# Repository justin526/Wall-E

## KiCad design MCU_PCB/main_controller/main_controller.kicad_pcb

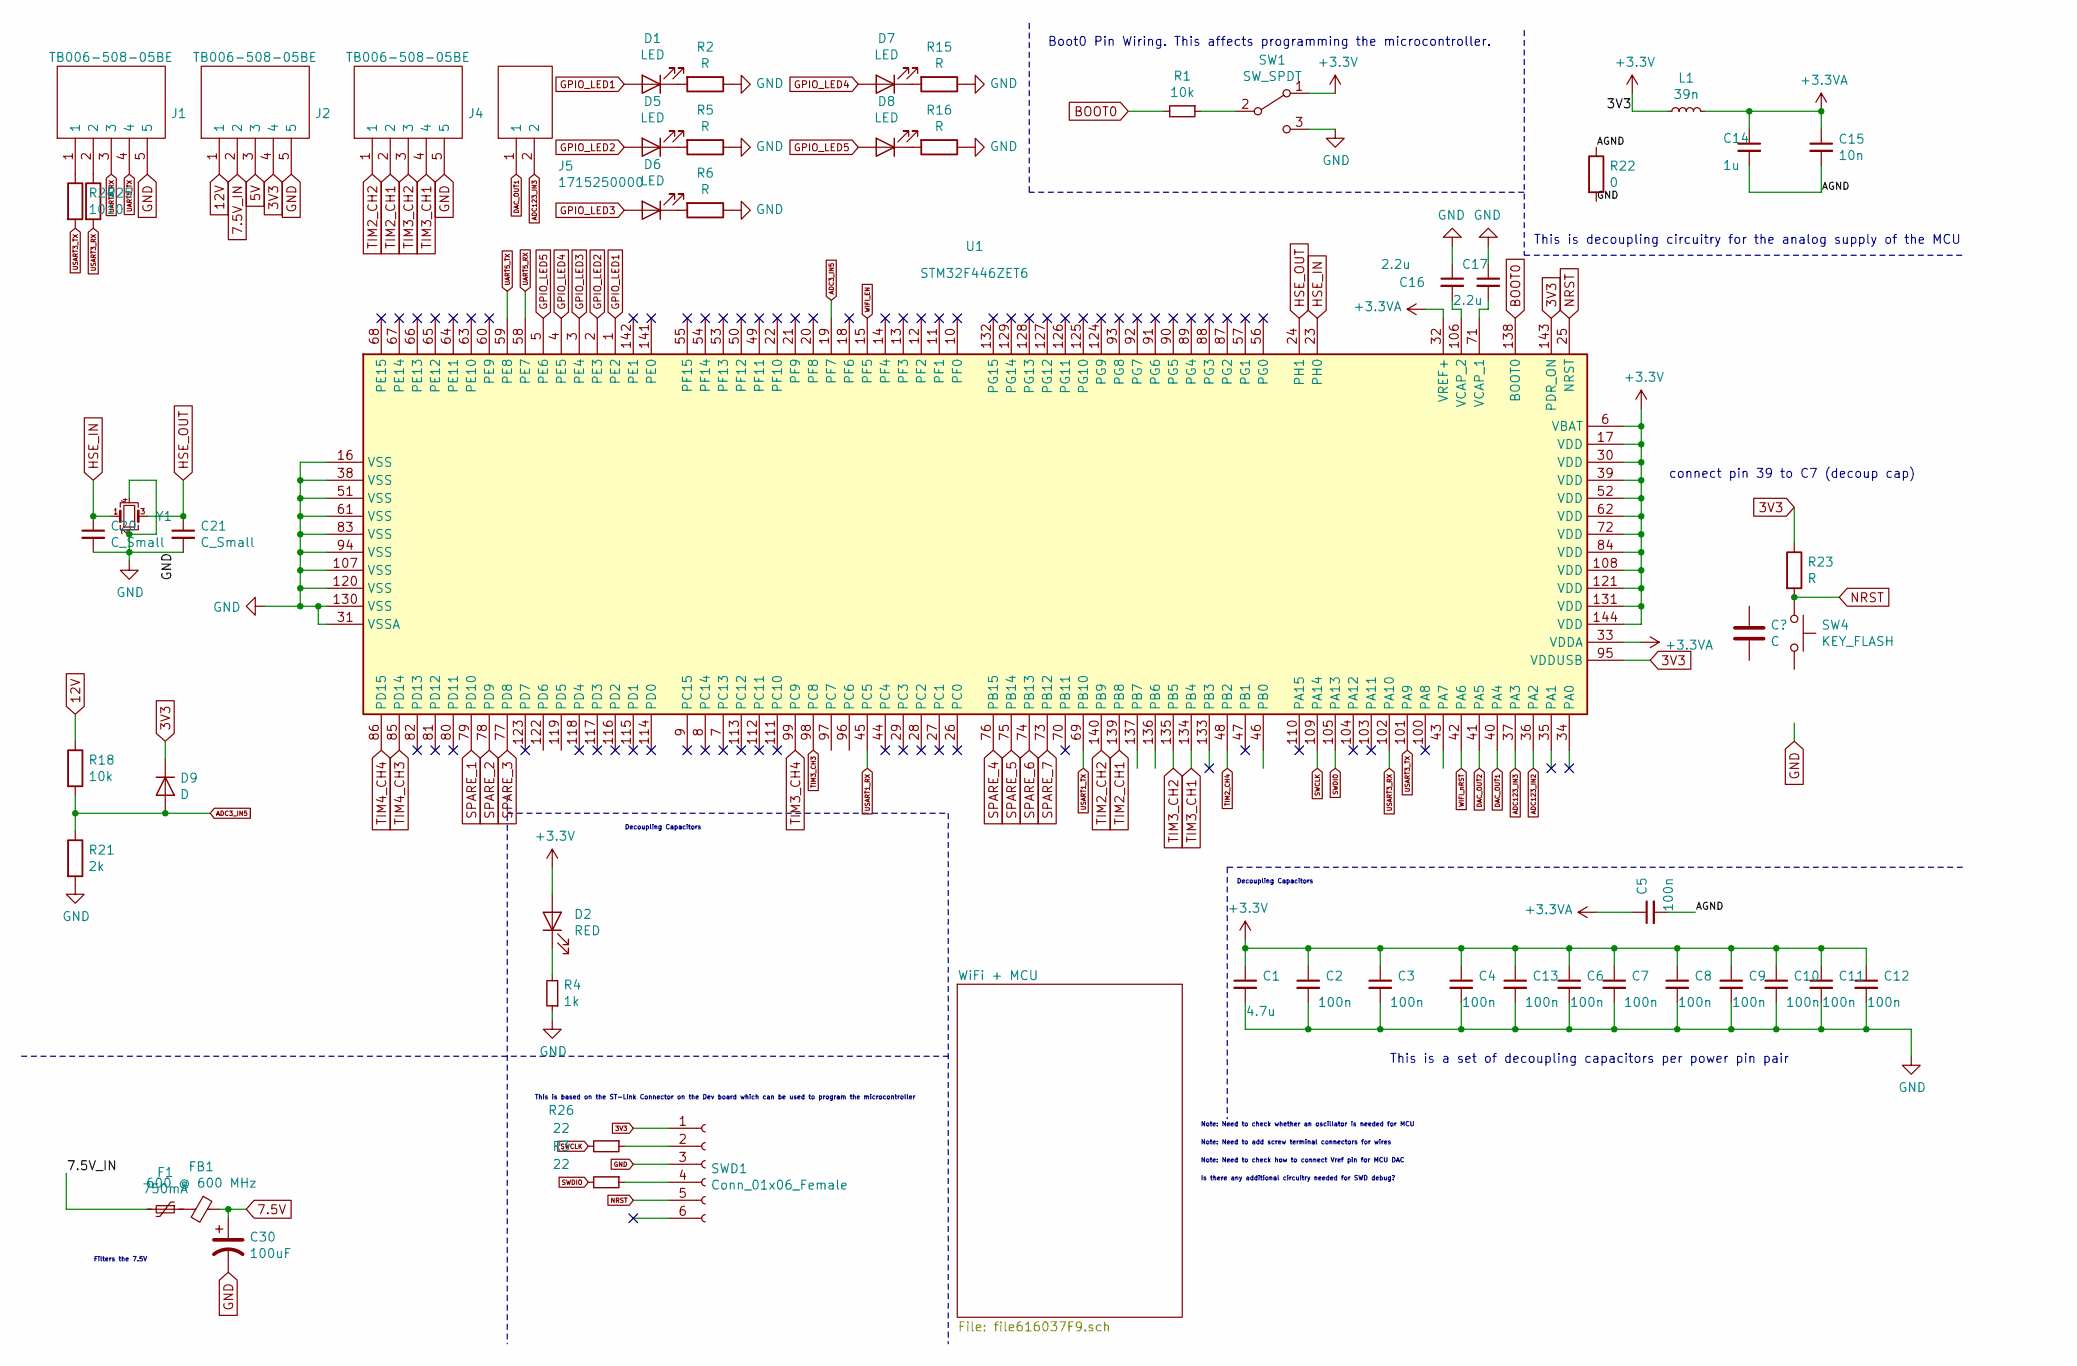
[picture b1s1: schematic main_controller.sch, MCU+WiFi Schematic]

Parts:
C1: 4.7u; C_0805_2012Metric
C2, C3, C4, C5, C6, C7, C8, C9, C10, C11, C12, C13: 100n; C_0805_2012Metric
C14: 1u; C_0805_2012Metric
C15: 10n; C_0805_2012Metric
C16, C17: 2.2u; C_0805_2012Metric
C20, C21: C_Small; C_0805_2012Metric
C30: 100uF; CAP_EEEHA0J101WR
D1, D5, D6, D7, D8: LED; LED_0805_2012Metric
D2: RED; LED_0805_2012Metric
D9: D; D_0805_2012Metric
F1: 750mA; R_1210_3225Metric
FB1: 600 @ 600 MHz; R_0603_1608Metric
J1, J2, J4: TB006-508-05BE; SHDR5W100P0X508_1X5_2540X820X1000P; Mouser Part Number 490-TB006-508-05BE
J5: 1715250000; Mouser Part Number 470-1715250000
L1: 39n; L_0402_1005Metric
R1, R18: 10k; R_0805_2012Metric
R2, R5, R6, R15, R16, R23: R; R_0805_2012Metric
R3, R26: 22; R_0805_2012Metric
R4: 1k; R_0805_2012Metric
R21: 2k; R_0805_2012Metric
R22: 0; R_0805_2012Metric
R24, R25: 10; R_0805_2012Metric
SW1: SW_SPDT; 118251376
SW4: KEY_FLASH; SW_147873-2
SWD1: Conn_01x06_Female; PinHeader_1x06_P2.54mm_Vertical
U1: STM32F446ZET6; LQFP-144_20x20mm_P0.5mm
Y1: Crystal_GND24_Small; EA1620LA1216000MTR

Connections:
3V3: C1.1, C2.1, C3.1, C4.1, C6.1, C7.1, C8.1, C9.1, C10.1, C11.1, C12.1, C13.1, D2.2 (A), D9.1 (K), J2.4, L1.1, R23.1, SW1.1 (A), SWD1.1, U1.6 (VBAT), U1.17 (VDD), U1.30 (VDD), U1.39 (VDD), U1.42 (PA6), U1.52 (VDD), U1.62 (VDD), U1.72 (VDD), U1.84 (VDD), U1.95 (VDDUSB), U1.108 (VDD), U1.121 (VDD), U1.131 (VDD), U1.143 (PDR_ON), U1.144 (VDD); also elsewhere on the board
5V: J2.3; also elsewhere on the board
7.5V: C30.1, FB1.1; also elsewhere on the board
7.5V_IN: F1.2, J2.2
12V: J2.1, R18.1
+3.3VA: C5.1, C14.1, C15.1, L1.2, U1.32 (VREF+), U1.33 (VDDA)
/AGND: C5.2, C14.2, C15.2, R22.1
ADC3_IN5: D9.2 (A), R18.2, R21.1, U1.19 (PF7)
ADC123_IN2: U1.36 (PA2)
ADC123_IN3: J5.2, U1.37 (PA3)
BOOT0: R1.2, U1.138 (BOOT0)
DAC_OUT1: J5.1, U1.40 (PA4)
DAC_OUT2: U1.41 (PA5)
GND: C1.2, C2.2, C3.2, C4.2, C6.2, C7.2, C8.2, C9.2, C10.2, C11.2, C12.2, C13.2, C16.1, C17.1, C20.2, C21.2, C30.2, J1.5, J2.5, J4.5, R2.1, R4.1, R5.1, R6.1, R15.1, R16.1, R21.2, R22.2, SW1.3 (C), SW4.2, SWD1.3, U1.16 (VSS), U1.31 (VSSA), U1.38 (VSS), U1.51 (VSS), U1.61 (VSS), U1.83 (VSS), U1.94 (VSS), U1.107 (VSS), U1.120 (VSS), U1.130 (VSS), Y1.2, Y1.4; also elsewhere on the board
GPIO_LED1: D1.2 (A), U1.1 (PE2)
GPIO_LED2: D5.2 (A), U1.2 (PE3)
GPIO_LED3: D6.2 (A), U1.3 (PE4)
GPIO_LED4: D7.2 (A), U1.4 (PE5)
GPIO_LED5: D8.2 (A), U1.5 (PE6)
HSE_IN: C20.1, U1.23 (PH0), Y1.1
HSE_OUT: C21.1, U1.24 (PH1), Y1.3
NRST: R23.2, SW4.1, SWD1.5, U1.25 (NRST)
unnamed: C16.2, U1.106 (VCAP_2)
unnamed: C17.2, U1.71 (VCAP_1)
unnamed: D1.1 (K), R2.2
unnamed: D2.1 (K), R4.2
unnamed: D5.1 (K), R5.2
unnamed: D6.1 (K), R6.2
unnamed: D7.1 (K), R15.2
unnamed: D8.1 (K), R16.2
unnamed: F1.1, FB1.2
unnamed: J1.1, R24.1
unnamed: J1.2, R25.1
unnamed: R1.1, SW1.2 (B)
unnamed: R3.1, SWD1.4
unnamed: R26.1, SWD1.2
SPARE_1: U1.79 (PD10)
SPARE_2: U1.78 (PD9)
SPARE_3: U1.77 (PD8)
SPARE_4: U1.76 (PB15)
SPARE_5: U1.75 (PB14)
SPARE_6: U1.74 (PB13)
SPARE_7: U1.73 (PB12)
SWCLK: R26.2, U1.109 (PA14)
SWDIO: R3.2, U1.105 (PA13)
TIM2_CH1: J4.2, U1.139 (PB8)
TIM2_CH2: J4.1, U1.140 (PB9)
TIM2_CH4: U1.48 (PB2)
TIM3_CH1: J4.4, U1.134 (PB4)
TIM3_CH2: J4.3, U1.135 (PB5)
TIM3_CH3: U1.98 (PC8)
TIM3_CH4: U1.99 (PC9)
TIM4_CH3: U1.85 (PD14)
TIM4_CH4: U1.86 (PD15)
UART5_RX: J1.3, U1.58 (PE7)
UART5_TX: J1.4, U1.59 (PE8)
USART1_RX: U1.45 (PC5); also elsewhere on the board
USART1_TX: U1.69 (PB10); also elsewhere on the board
USART3_RX: R25.2, U1.102 (PA10)
USART3_TX: R24.2, U1.101 (PA9)
WIFI_EN: U1.15 (PF5); also elsewhere on the board

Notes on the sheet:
Boot0 Pin Wiring. This affects programming the microcontroller.
This is a set of decoupling capacitors per power pin pair
This is decoupling circuitry for the analog supply of the MCU
Note: Need to check whether an oscillator is needed for MCU
Filters the 7.5V
This is based on the ST-Link Connector on the Dev board which can be used to program the microcontroller
Note: Need to add screw terminal connectors for wires
Note: Need to check how to connect Vref pin for MCU DAC
Is there any additional circuitry needed for SWD debug?
Decoupling Capacitors
connect pin 39 to C7 (decoup cap)

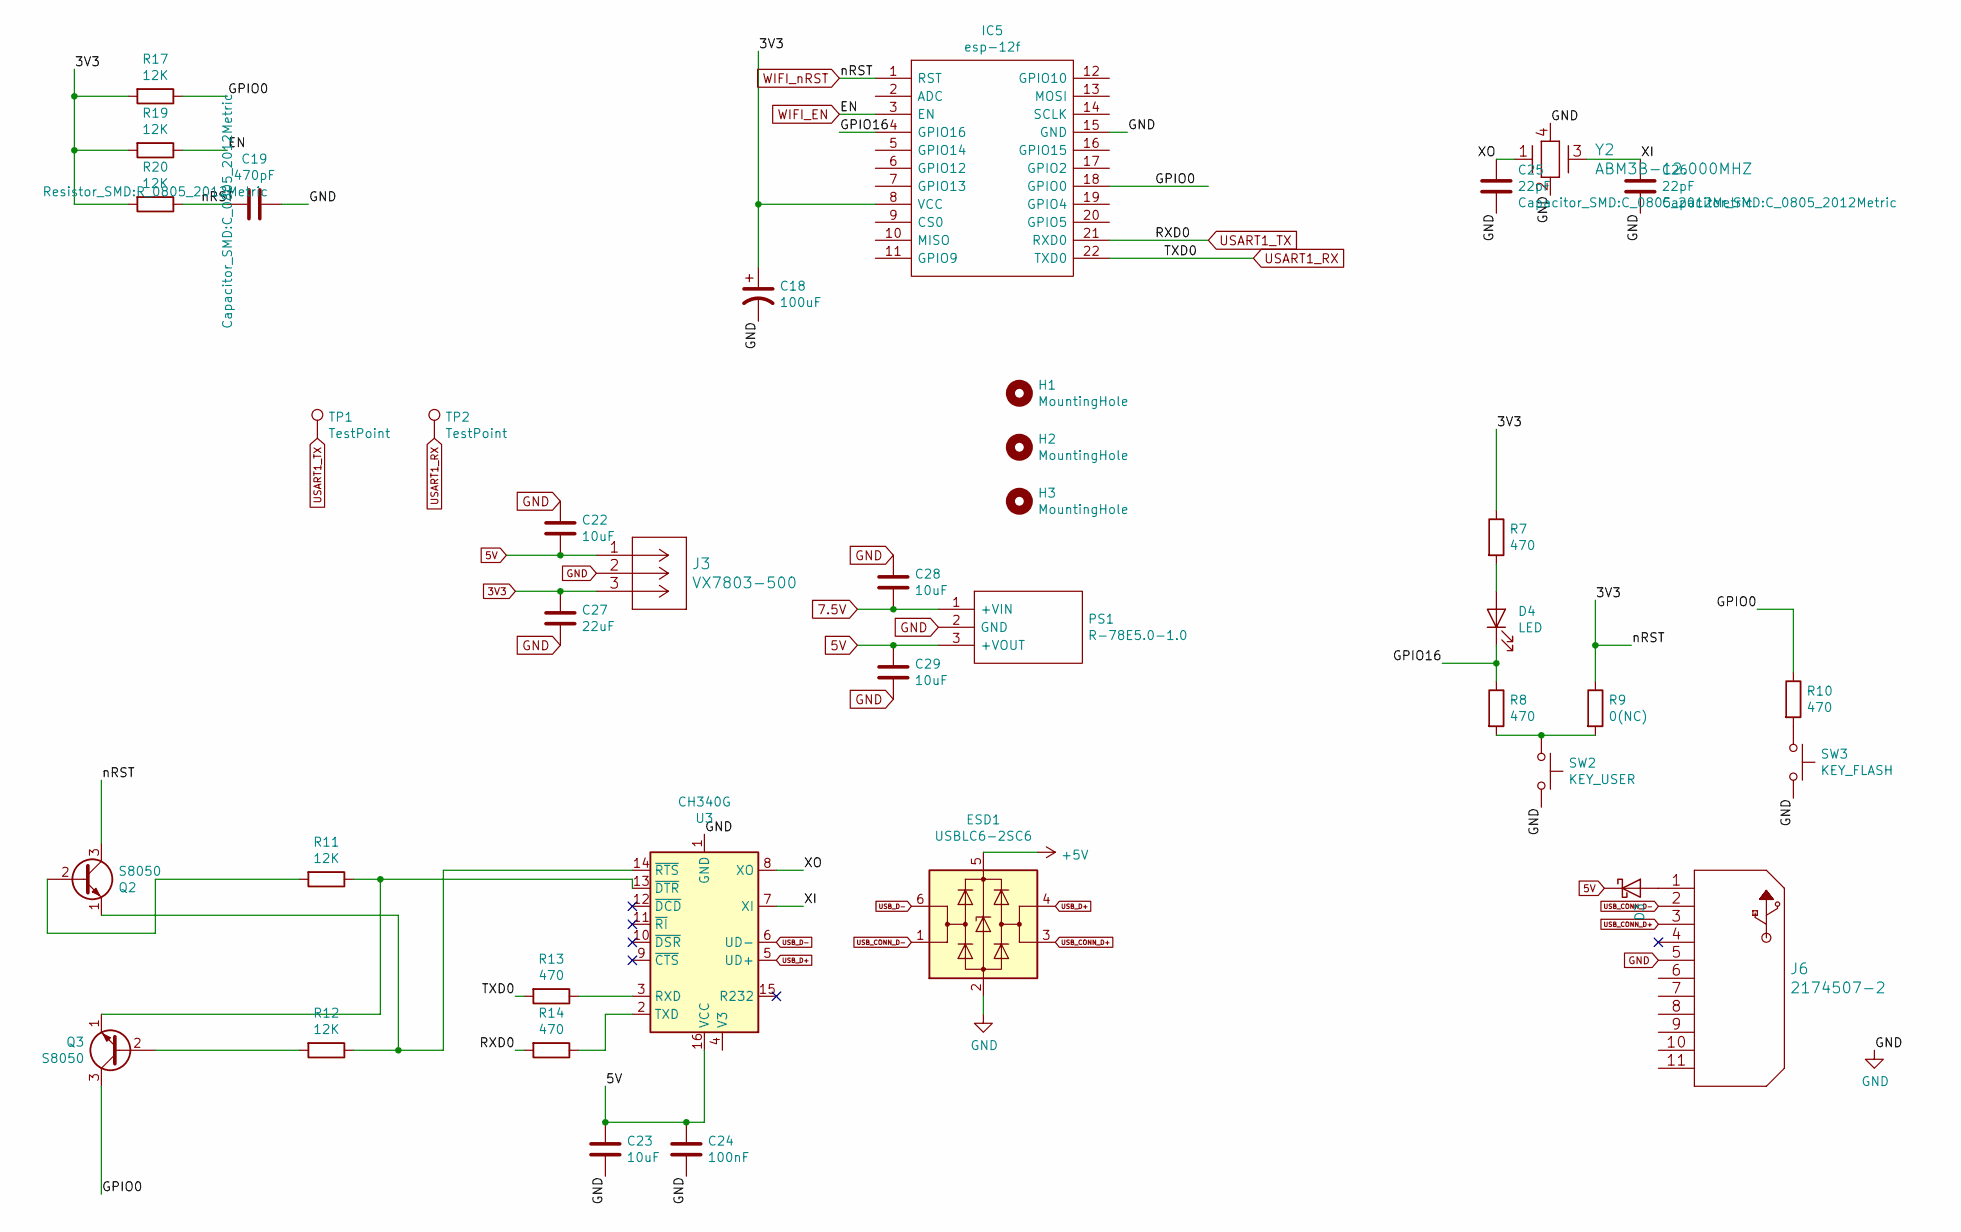
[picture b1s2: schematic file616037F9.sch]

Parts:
C18: 100uF; CAP_EEEHA0J101WR
C19: 470pF; C_0805_2012Metric
C22, C28, C29: 10uF; C_1210_3225Metric
C23: 10uF; C_0805_2012Metric
C24: 100nF; C_0805_2012Metric
C25, C26: 22pF; C_0805_2012Metric
C27: 22uF; C_1210_3225Metric
D3: D_Schottky; 1N4007G-T
D4: LED; LED_0805_2012Metric
ESD1: USBLC6-2SC6; SOT-23-6
H1, H2, H3: MountingHole; MountingHole_2.2mm_M2
IC5: esp-12f; esp12f; Manufacturer_Part_Number esp-12f
J3: VX7803-500
J6: 2174507-2
PS1: R-78E5.0-1.0; R78E5010; Mouser Part Number 919-R-78E5.0-1.0
Q2, Q3: S8050; TO-92_Inline
R7, R8, R10, R13, R14: 470; R_0805_2012Metric
R9: 0(NC); R_0805_2012Metric
R11, R12, R17, R19, R20: 12K; R_0805_2012Metric
SW2: KEY_USER; SW_147873-2
SW3: KEY_FLASH; SW_147873-2
TP1, TP2: TestPoint; KEYSTONE_5000
U3: CH340G; SOIC-16_3.9x9.9mm_P1.27mm
Y2: ABM3B-12.000MHZ

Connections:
3V3: C18.1, C19.2, C27.1, IC5.1 (RST), IC5.8 (VCC), J3.3, Q2.3 (C), R7.1, R9.1, R17.2, R19.2, R20.1, R20.2; also elsewhere on the board
5V: C22.2, C23.1, C24.1, C29.1, D3.1 (K), J3.1, PS1.3 (+VOUT), U3.16 (VCC); also elsewhere on the board
7.5V: C28.2, PS1.1 (+VIN); also elsewhere on the board
+5V: ESD1.5 (VBUS)
/WiFi + MCU/GPIO0: IC5.18 (GPIO0), Q3.3 (C), R10.1, R17.1
/WiFi + MCU/GPIO16: D4.1 (K), IC5.4 (GPIO16), R8.1
/WiFi + MCU/XI: C26.1, U3.7 (XI), Y2.3 (2)
/WiFi + MCU/XO: C25.1, U3.8 (XO), Y2.1
GND: C18.2, C19.1, C22.1, C23.2, C24.2, C25.2, C26.2, C27.2, C28.1, C29.2, ESD1.2 (GND), IC5.15 (GND), J3.2, J6.5, PS1.2 (GND), SW2.2, SW3.2, U3.1 (GND), Y2.2 (GND), Y2.4 (GND); also elsewhere on the board
unnamed: D3.2 (A), J6.1
unnamed: D4.2 (A), R7.2
unnamed: Q2.1 (E), R12.1, U3.14 (~RTS)
unnamed: Q2.2 (B), R11.2
unnamed: Q3.1 (E), R11.1, U3.13 (~DTR)
unnamed: Q3.2 (B), R12.2
unnamed: R8.2, R9.2, SW2.1
unnamed: R10.2, SW3.1
unnamed: R13.1, U3.3 (RXD)
unnamed: R14.1, U3.2 (TXD)
USART1_RX: IC5.22 (TXD0), R13.2, TP2.1; also elsewhere on the board
USART1_TX: IC5.21 (RXD0), R14.2, TP1.1; also elsewhere on the board
USB_CONN_D+: ESD1.3 (I/O2), J6.3
USB_CONN_D-: ESD1.1 (I/O1), J6.2
USB_D+: ESD1.4 (I/O2), U3.5 (UD+)
USB_D-: ESD1.6 (I/O1), U3.6 (UD-)
WIFI_EN: IC5.3 (EN), R19.1; also elsewhere on the board

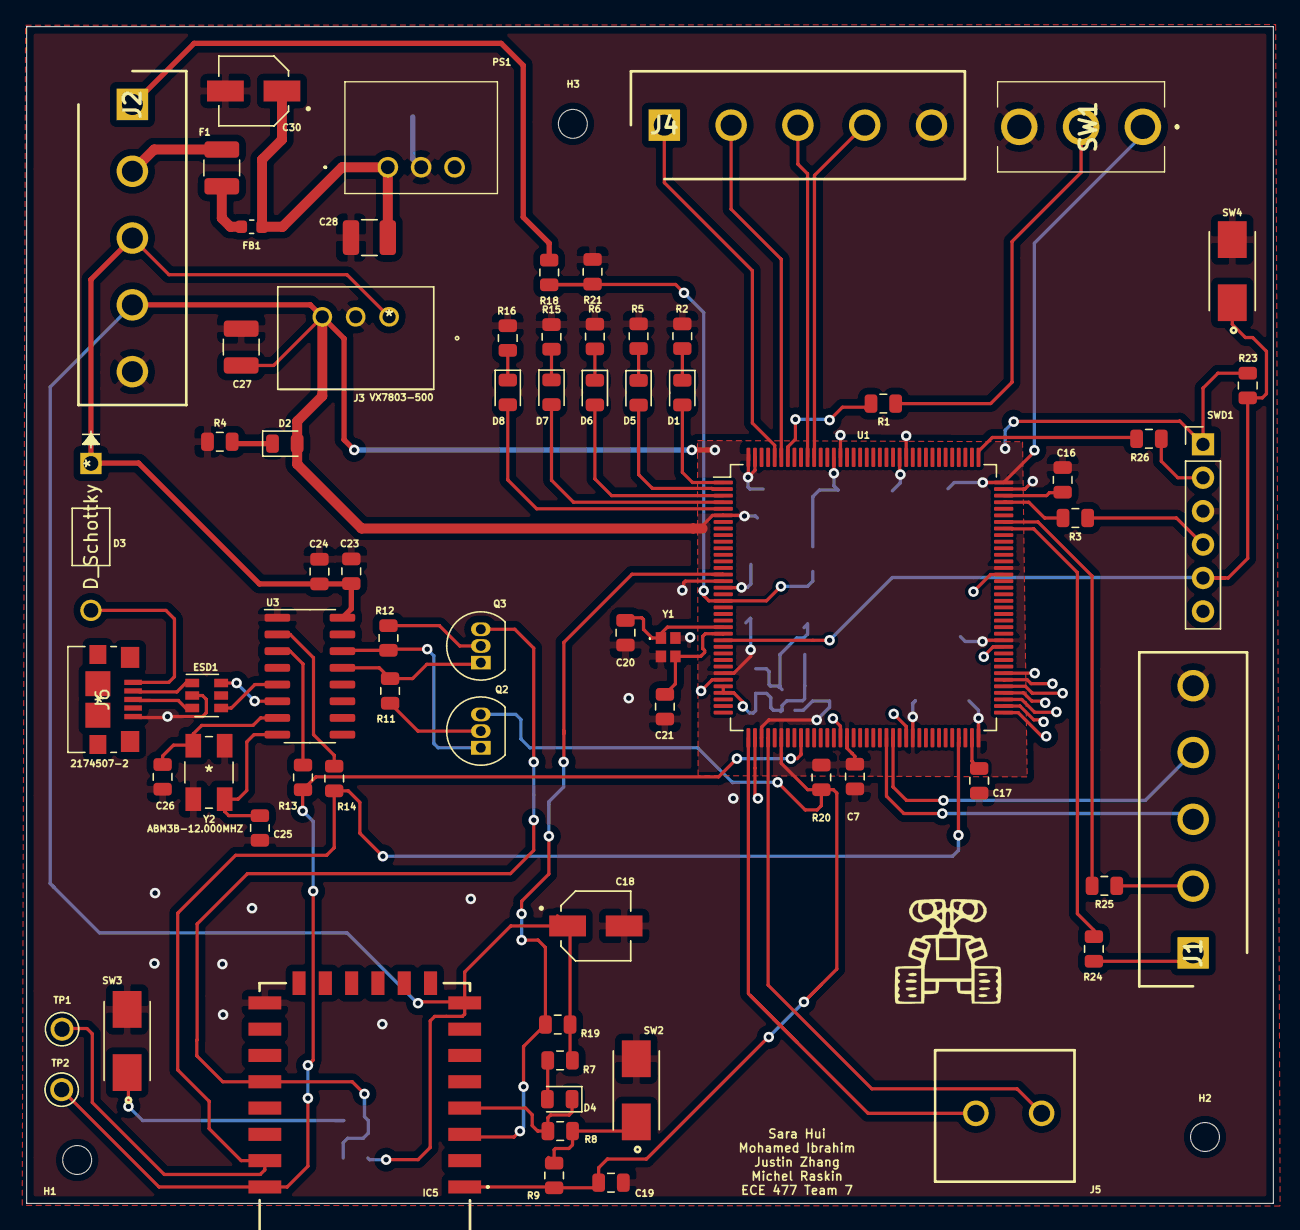
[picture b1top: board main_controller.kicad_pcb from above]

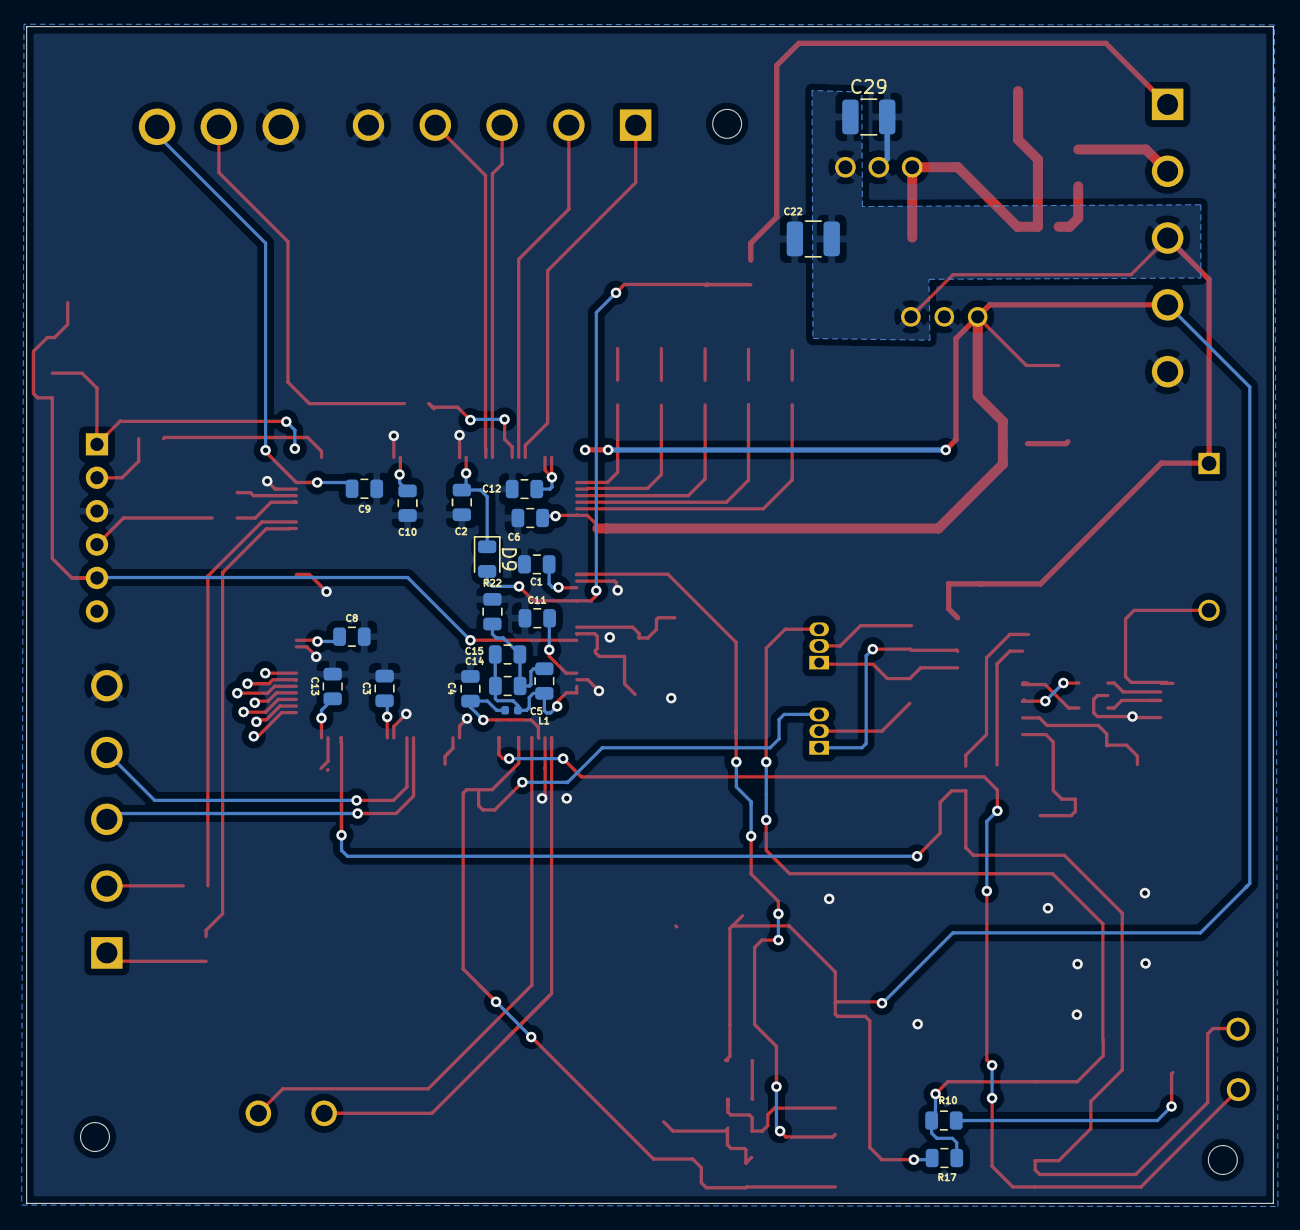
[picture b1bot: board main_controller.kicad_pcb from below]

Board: 2 copper layers, 94.8 x 89.5 mm, 93 parts (21 on the bottom side), 65 nets.

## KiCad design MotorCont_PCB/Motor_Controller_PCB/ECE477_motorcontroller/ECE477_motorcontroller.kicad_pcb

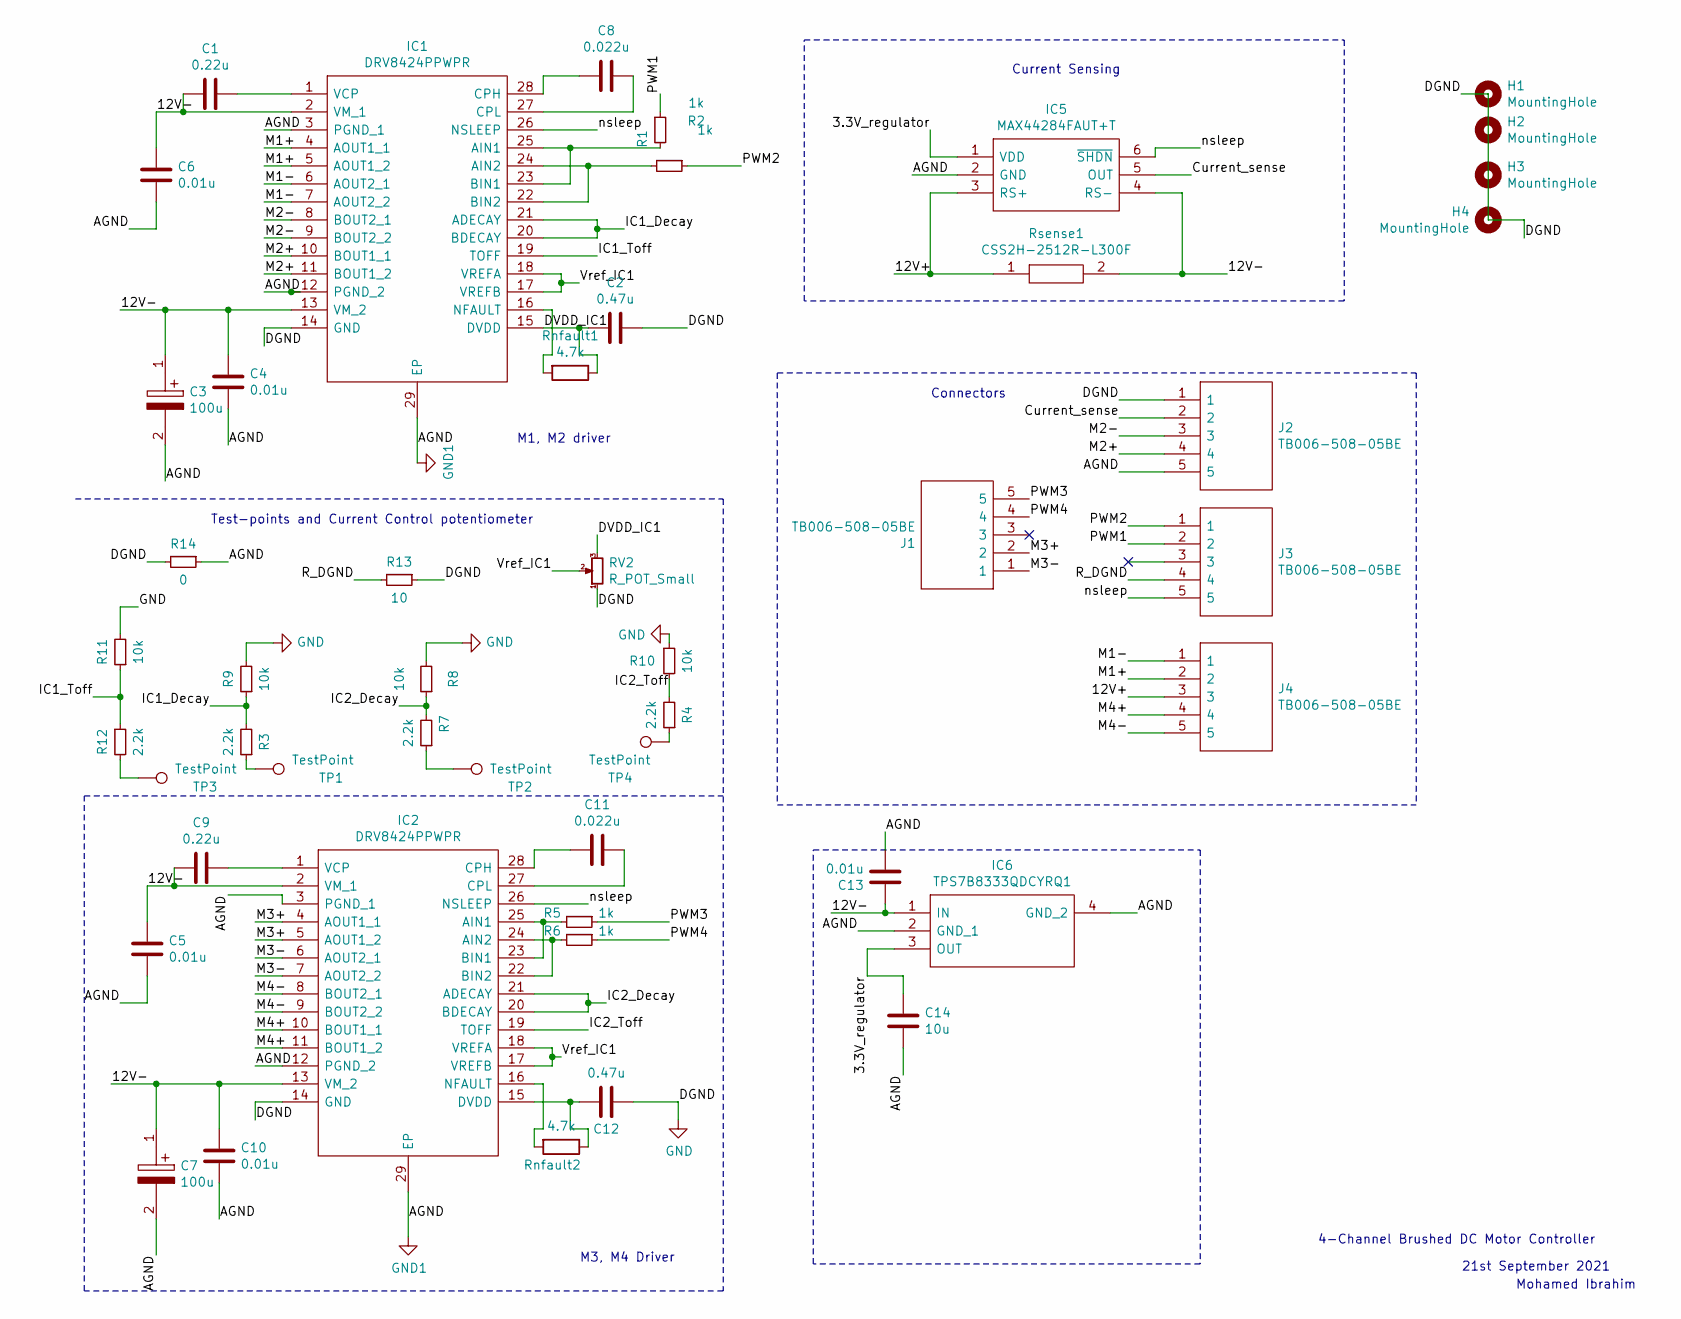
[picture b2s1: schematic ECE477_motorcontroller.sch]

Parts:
C1, C9: 0.22u; CAPC1005X55N
C2, C12: 0.47u; CAPC1005X55N
C3, C7: 100u; CAPPRD350W60D840H1350; Mouser Part Number 647-UBT1C101MPD8TD
C4, C5, C6, C10, C13: 0.01u; CAPC1005X55N
C8, C11: 0.022u; CAPC3216X88N
C14: 10u; C_1210_3225Metric
H1, H2, H3, H4: MountingHole; MountingHole_2.2mm_M2
IC1, IC2: DRV8424PPWPR; SOP65P640X120-29N; Mouser Part Number 595-DRV8424PPWPR
IC5: MAX44284FAUT+T; SOT95P280X145-6N; Mouser Part Number 700-MAX44284FAUT+T
IC6: TPS7B8333QDCYRQ1; SOT230P700X180-4N; Mouser Part Number 595-TPS7B8333QDCYRQ1
J1, J2, J3, J4: TB006-508-05BE; SHDR5W100P0X508_1X5_2540X820X1000P; Mouser Part Number 490-TB006-508-05BE
R1, R2, R5, R6: 1k; R_0805_2012Metric
R3, R4, R7, R12: 2.2k; R_0805_2012Metric
R8, R9, R10, R11: 10k; R_0805_2012Metric
R13: 10; R_0805_2012Metric
R14: 0; R_0805_2012Metric
RV2: R_POT_Small; TRIM_3362P-1-253LF
Rnfault1, Rnfault2: 4.7k; RESC1005X37N
Rsense1: CSS2H-2512R-L300F; CSS2H2512RL300F; Mouser Part Number 652-CSS2H-2512RL300F
TP1, TP2, TP3, TP4: TestPoint; KEYSTONE_5000

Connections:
/3.3V_regulator: C14.1, IC5.1 (VDD), IC6.3 (OUT)
/12V+: IC5.3 (RS+), J4.3, Rsense1.1
/12V-: C1.2, C3.1, C4.1, C5.1, C6.1, C7.1, C9.2, C10.1, C13.1, IC1.2 (VM_1), IC1.13 (VM_2), IC2.2 (VM_1), IC2.13 (VM_2), IC5.4 (RS-), IC6.1 (IN), Rsense1.2
/Current_sense: IC5.5 (OUT), J2.2
/DVDD_IC1: C2.1, IC1.15 (DVDD), RV2.3, Rnfault1.1
/IC1_Decay: IC1.20 (BDECAY), IC1.21 (ADECAY), R3.2, R9.1
/IC1_Toff: IC1.19 (TOFF), R11.1, R12.1
/IC2_Decay: IC2.20 (BDECAY), IC2.21 (ADECAY), R7.2, R8.1
/IC2_Toff: IC2.19 (TOFF), R4.2, R10.2
/M1+: IC1.4 (AOUT1_1), IC1.5 (AOUT1_2), J4.2
/M1-: IC1.6 (AOUT2_1), IC1.7 (AOUT2_2), J4.1
/M2+: IC1.10 (BOUT1_1), IC1.11 (BOUT1_2), J2.4
/M2-: IC1.8 (BOUT2_1), IC1.9 (BOUT2_2), J2.3
/M3+: IC2.4 (AOUT1_1), IC2.5 (AOUT1_2), J1.2
/M3-: IC2.6 (AOUT2_1), IC2.7 (AOUT2_2), J1.1
/M4+: IC2.10 (BOUT1_1), IC2.11 (BOUT1_2), J4.4
/M4-: IC2.8 (BOUT2_1), IC2.9 (BOUT2_2), J4.5
/PWM1: J3.2, R1.1
/PWM2: J3.1, R2.1
/PWM3: J1.5, R5.1
/PWM4: J1.4, R6.1
/R_DGND: J3.4, R13.2
/Vref_IC1: IC1.17 (VREFB), IC1.18 (VREFA), IC2.17 (VREFB), IC2.18 (VREFA), RV2.2
/nsleep: IC1.26 (NSLEEP), IC2.26 (NSLEEP), IC5.6 (~SHDN), J3.5
GND: C2.2, C12.2, IC1.14 (GND), IC2.14 (GND), J2.1, R8.2, R9.2, R10.1, R11.2, R13.1, R14.2, RV2.1
GND1: C3.2, C4.2, C5.2, C6.2, C7.2, C10.2, C13.2, C14.2, IC1.3 (PGND_1), IC1.12 (PGND_2), IC1.29 (EP), IC2.3 (PGND_1), IC2.12 (PGND_2), IC2.29 (EP), IC5.2 (GND), IC6.2 (GND_1), IC6.4 (GND_2), J2.5, R14.1
unnamed: C1.1, IC1.1 (VCP)
unnamed: C8.1, IC1.27 (CPL)
unnamed: C8.2, IC1.28 (CPH)
unnamed: C9.1, IC2.1 (VCP)
unnamed: C11.1, IC2.27 (CPL)
unnamed: C11.2, IC2.28 (CPH)
unnamed: C12.1, IC2.15 (DVDD), Rnfault2.1
unnamed: IC1.16 (NFAULT), Rnfault1.2
unnamed: IC1.22 (BIN2), IC1.24 (AIN2), R2.2
unnamed: IC1.23 (BIN1), IC1.25 (AIN1), R1.2
unnamed: IC2.16 (NFAULT), Rnfault2.2
unnamed: IC2.22 (BIN2), IC2.24 (AIN2), R6.2
unnamed: IC2.23 (BIN1), IC2.25 (AIN1), R5.2
unnamed: R3.1, TP1.1
unnamed: R4.1, TP4.1
unnamed: R7.1, TP2.1
unnamed: R12.2, TP3.1

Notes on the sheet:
Connectors
M1, M2 driver
M3, M4 Driver
Current Sensing
4-Channel Brushed DC Motor Controller
21st September 2021
Mohamed Ibrahim
Test-points and Current Control potentiometer

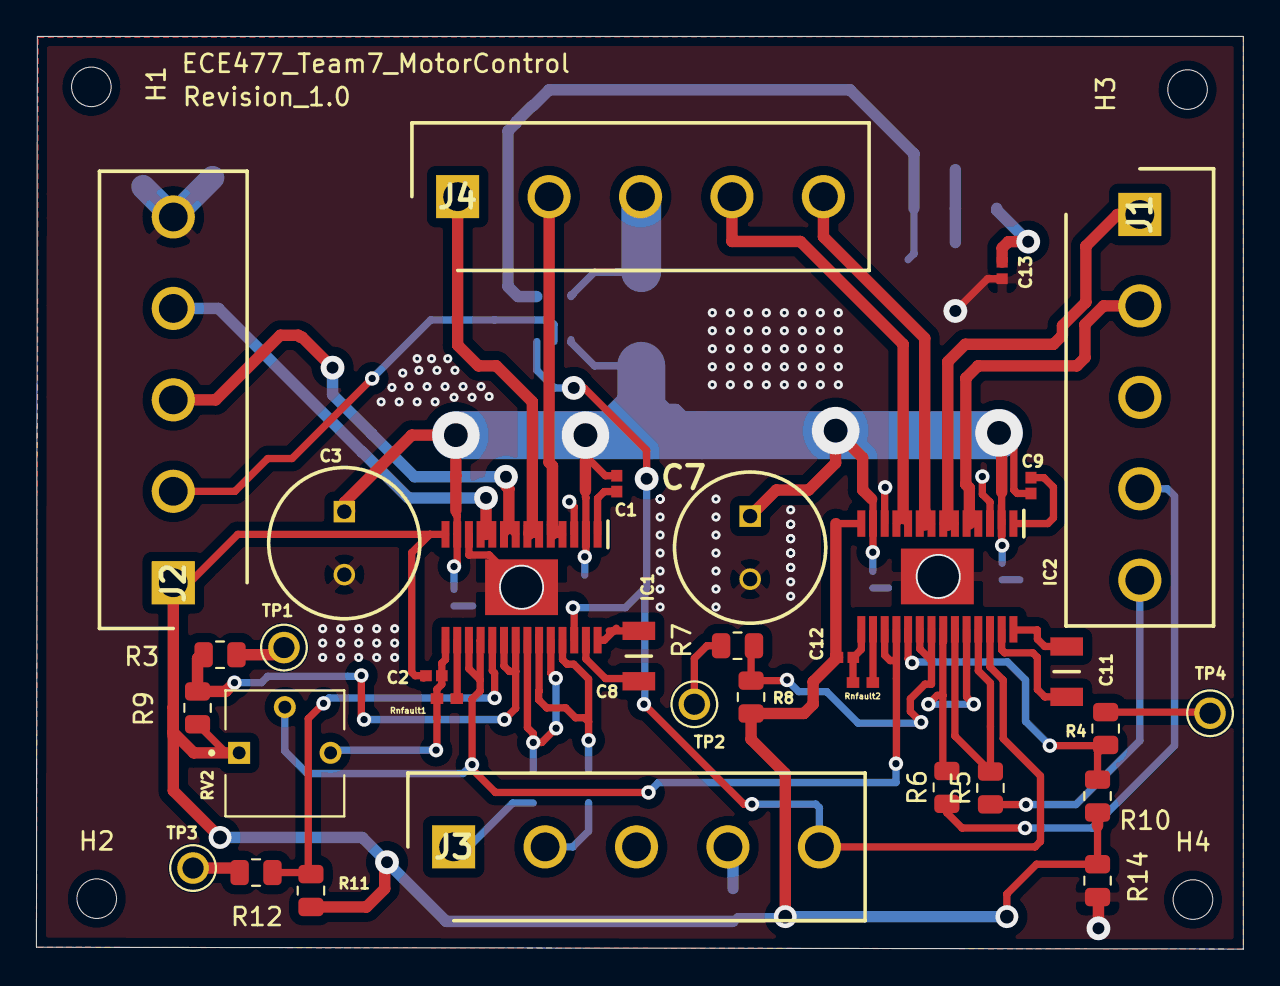
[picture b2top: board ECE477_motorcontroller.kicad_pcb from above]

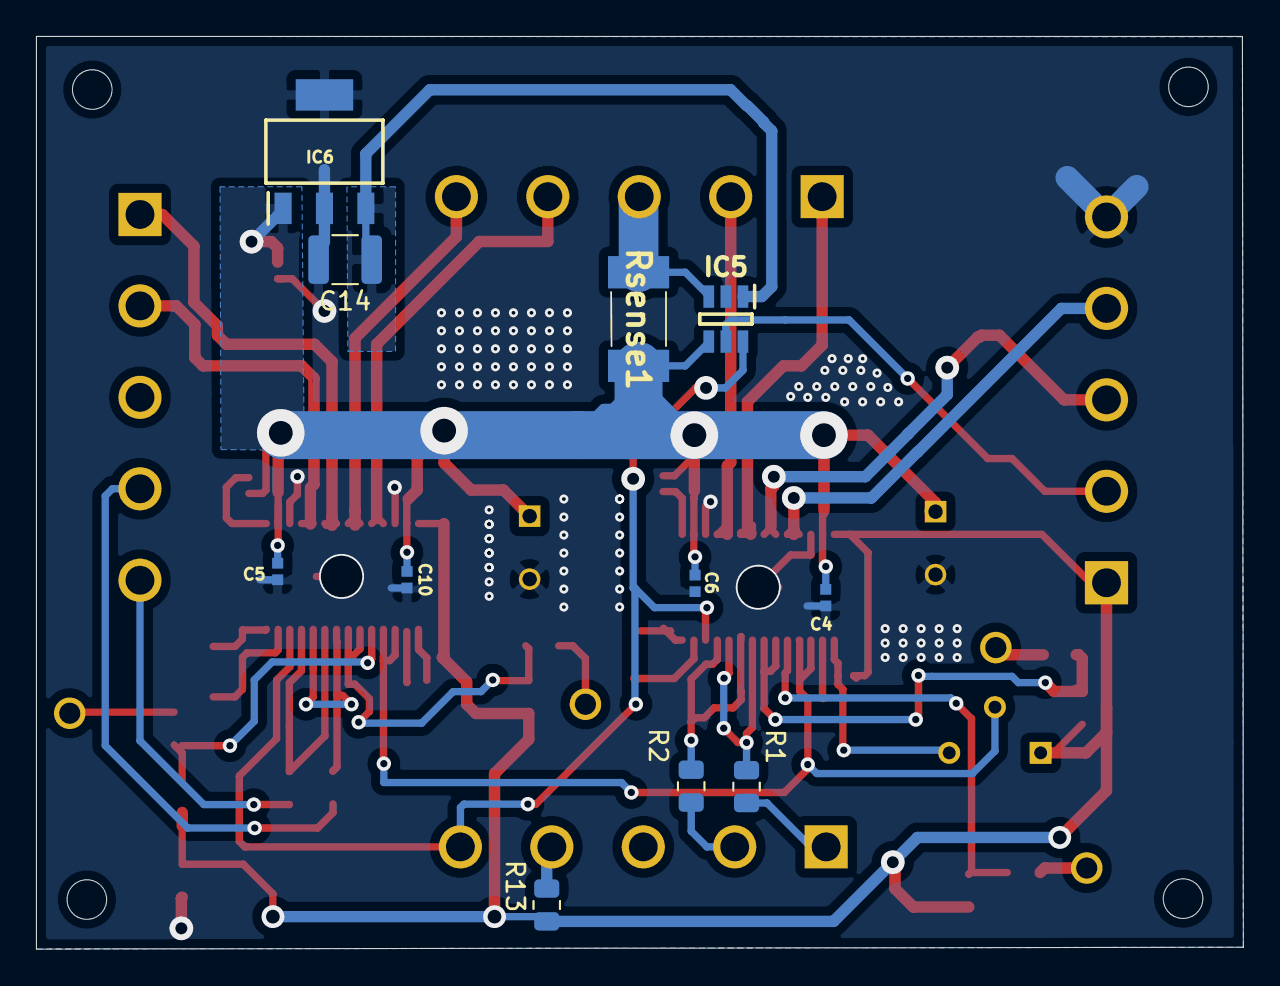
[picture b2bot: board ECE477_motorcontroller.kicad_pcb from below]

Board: 2 copper layers, 67.0 x 50.7 mm, 48 parts (11 on the bottom side), 43 nets.

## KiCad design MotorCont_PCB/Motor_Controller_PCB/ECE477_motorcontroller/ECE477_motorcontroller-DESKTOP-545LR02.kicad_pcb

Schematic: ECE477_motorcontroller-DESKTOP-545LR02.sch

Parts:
Blue_LED1: LED; C503B-BCN
C1, C9, C19, C20: 0.22u; CAPC1005X55N
C2, C12, C24, C26: 0.47u; CAPC1005X55N
C3, C7, C16, C18: 100u; CAPPRD350W60D840H1350; Mouser Part Number 647-UBT1C101MPD8TD
C4, C5, C6, C10, C13, C14, C15, C17, C21, C22: 0.01u; CAPC1005X55N
C8, C11, C23, C25: 0.022u; CAPC3216X88N
IC1, IC2, IC3, IC4: DRV8424PPWPR; SOP65P640X120-29N; Mouser Part Number 595-DRV8424PPWPR
IC5: MAX44284FAUT+T; SOT95P280X145-6N; Mouser Part Number 700-MAX44284FAUT+T
IC6: TPS7B8333QDCYRQ1; SOT230P700X180-4N; Mouser Part Number 595-TPS7B8333QDCYRQ1
J1: 1988930; Mouser Part Number 651-1988930
J2: Conn_01x05_Female; PinSocket_1x05_P2.54mm_Vertical
LED1: LTL2T3TGK6; Mouser Part Number 859-LTL2T3TGK6
R1: CSS2H-2512R-L300F; CSS2H2512RL300F; Mouser Part Number 652-CSS2H-2512RL300F
R_SleepLED1, R_SleepLED2: 330; RESC1608X55N
R_sleep1: 1k; RESC1005X37N
Rnfault1, Rnfault2, Rnfault3, Rnfault4: 4.7k; RESC1005X37N
Switch1: D6R60F1LFS; D6R40F1LFS; Mouser Part Number 611-D6R60F1LFS
U1: STN1NK60Z

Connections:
/3.3V_regulator: C14.1, IC5.1, IC6.3 (OUT), LED1.1, R_sleep1.1, Switch1.1
/12V_supply: IC5.3, J1.11, R1.1
/Current_sense: IC5.5, J2.2
/M1+: IC1.4, J1.4
/M1-: IC1.6, J1.5
/M2+: IC2.4, J1.6
/M2-: IC2.6, J1.7
/M3+: IC3.4, J1.8
/M3-: IC3.6, J1.9
/M4+: IC4.4, J1.10
/M4-: IC4.6, J1.14
/MCU_DAC: IC1.17, IC1.18, IC2.17, IC2.18, IC3.17, IC3.18, IC4.17, IC4.18, J2.1
/PWM1: IC1.25, IC3.25, J1.1
/PWM2: IC1.24, IC3.24, J1.2
/PWM3: IC2.25, IC4.25, J1.3
/PWM4: IC2.24, IC4.24, J1.15
/Vm: C1.2, C3.1, C4.1, C5.1, C6.1, C7.1, C9.2, C10.1, C13.1, C15.1, C16.1, C17.1, C18.1, C19.2, C20.2, C21.1, C22.1, IC1.2, IC1.13, IC2.2, IC2.13, IC3.2, IC3.13, IC4.2, IC4.13, IC5.4, IC6.1 (IN), R1.2
/nsleep: IC1.26, IC2.26, IC3.26, IC4.26, IC5.6, R_sleep1.2, U1.2
GND: C2.2, C12.2, C24.2, C26.2, IC1.14, IC1.19, IC1.20, IC1.21, IC1.22, IC1.23, IC2.14, IC2.19, IC2.20, IC2.21, IC2.22, IC2.23, IC3.14, IC3.19, IC3.20, IC3.21, IC3.22, IC3.23, IC4.14, IC4.19, IC4.20, IC4.21, IC4.22, IC4.23, IC6.4 (GND_2), J1.13, J2.3, J2.4, J2.5, R_SleepLED1.2, R_SleepLED2.2, U1.3
GND1: C3.2, C4.2, C5.2, C6.2, C7.2, C10.2, C13.2, C14.2, C15.2, C16.2, C17.2, C18.2, C21.2, C22.2, IC1.12, IC1.29, IC2.3, IC2.12, IC2.29, IC3.3, IC3.12, IC3.29, IC4.3, IC4.12, IC4.29, IC5.2, IC6.2 (GND_1), J1.12
unnamed: Blue_LED1.1, R_SleepLED1.1
unnamed: Blue_LED1.2, Switch1.4, U1.1
unnamed: C1.1, IC1.1
unnamed: C2.1, IC1.15, Rnfault1.1
unnamed: C8.1, IC1.27
unnamed: C8.2, IC1.28
unnamed: C9.1, IC2.1
unnamed: C11.1, IC2.27
unnamed: C11.2, IC2.28
unnamed: C12.1, IC2.15, Rnfault2.1
unnamed: C19.1, IC4.1
unnamed: C20.1, IC3.1
unnamed: C23.1, IC4.27
unnamed: C23.2, IC4.28
unnamed: C24.1, IC4.15, Rnfault4.1
unnamed: C25.1, IC3.27
unnamed: C25.2, IC3.28
unnamed: C26.1, IC3.15, Rnfault3.1
unnamed: IC1.16, Rnfault1.2
unnamed: IC2.16, Rnfault2.2
unnamed: IC3.16, Rnfault3.2
unnamed: IC4.16, Rnfault4.2
unnamed: LED1.2, R_SleepLED2.1

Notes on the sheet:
I still need to figure out whether I need to use the A/BDecay Pins and the use of Toff
This block is the reset block for all chips
Board is ON indicator
Connectors
M1 driver
M2 Driver
Current Sensing
4-Channel Brushed DC Motor Controller
21st September 2021
Mohamed Ibrahim

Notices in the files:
micro/Core/Src/stm32f4xx_hal_msp.c:
© Copyright (c) 2021 STMicroelectronics.
All rights reserved.
This software component is licensed by ST under BSD 3-Clause license,
the "License"; You may not use this file except in compliance with the
License. You may obtain a copy of the License at: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
(C) COPYRIGHT STMicroelectronics *****END OF FILE
parts and their libraries:
Copyright 2021 Accelerated Designs. All rights reserved.
